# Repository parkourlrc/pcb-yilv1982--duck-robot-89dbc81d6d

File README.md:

# duck-robot

MicroDuck 小型双足机器人的个人复刻项目。当前主线为**方案 C（社区套件，飞特 HD-1910-C001）**；组织原则是“硬件复刻与整机集成 → 核心硬件自主设计；运行软件参考适配；训练环境自主建设”。A/B 仅作来源与回退标签，不作为整个项目的一级分类。

**当前状态（2026-11-05）**
- **整机**：M1 已完成（用户确认 2026-11-05）：新单 3P 口 IMU 已换装、15 颗舵机标定完成；IMU 间歇缺答/行走摔倒转可靠性跟踪。
- **自主 HAT**：B.0 / `84362651` 已付款5片；[工厂MK701/Y701方向确认](docs/references/扩展板乙版降本/engineering-feedback/research.md)已核对，待用户回复；**研发继续暂停**，未确认发货，首板未验收，原750元目标未达成。
- **PCB 全流程**：M3 进行中，B.0 / `84362651`、Y10／SMT2611051346 已付款，等待回寄与上机测试。
- **训练**：M2 已完成（官方模型上机+基本动作，用户确认）；M4 自训进行中，自训策略尚未上机。
- **里程碑**：M1/M2 已闭环；M3 PCB 全流程进行中（已下单，待回寄/上机）；M4 自训进行中；见 [MILESTONES](MILESTONES.md)。

详见 [PROGRESS](PROGRESS.md)；物料与缺口见 [BOM](BOM.md)。

## 入口

| 文档 | 用途 |
|---|---|
| [AGENTS.md](AGENTS.md) | 项目规则、目录边界与协作要求；开始前先读 |
| [PROGRESS.md](PROGRESS.md) | 当前状态、阻塞、待办与按时间倒序的记录 |
| [BOM.md](BOM.md) | C 线物料、数量与采购状态 |
| [MILESTONES.md](MILESTONES.md) | 8 个里程碑、验收标准与当前状态 |
| [docs/pcb-production-runbook.md](docs/pcb-production-runbook.md) | PCB 从需求到回寄上机的逐步运行手册 |
| [docs/README.md](docs/README.md) | 方案、测试单、图纸、照片与研究索引 |
| [hardware/README.md](hardware/README.md) | 复刻整机、取电板与自主 HAT |
| [software/README.md](software/README.md) | 本机软件适配、robotd/Studio 与部署索引 |
| [tools/README.md](tools/README.md) | 嘉立创下单、烧录依赖与开发辅助 |
| [scripts/README.md](scripts/README.md) | 跨域维护与诊断脚本 |
| [duck-robot-training](https://gitee.com/yilv1982/duck-robot-training) | 自建 real2sim2real 训练工程与资料（2026-11-10 拆分） |
| [flash/README.md](flash/README.md) | IMU 固件与烧录 |
| [references/README.md](references/README.md) | 三个上游参考库（只读） |

## 三条主线

### 1. 硬件复刻与整机集成

整机基线、装配与接线以 [hardware/replica](hardware/replica/README.md)、[BOM](BOM.md) 和 [PROGRESS](PROGRESS.md) 为准。当前 C 线为 kissqy HAT（REVA）＋新单 3P 口 IMU＋15 颗 HD-1910-C001；白色 HAT V1.2 与旧 GD32/v0.3 板仅作历史。供电按 [v2 架构](docs/power-architecture-v2.md) 的讨论基线，实物复核见[供电与扩展板实物复核](docs/references/供电与扩展板实物复核/research.md)；旧的 [HAT V1.2 测试单](docs/hat-v1.2-test.md) 不自动套用到当前板。

### 2. 核心硬件自主设计

自主 HAT 工作区在 [hardware/custom_hat](hardware/custom_hat/README.md)：现行 B.0 源 `84362651`，2026-11-05 已付款 5 片、线路暂停，首板未验收；A.1 与旧检查点在 `rev_a`、`归档` 前缀中保留。方法与复盘见[研发流程](docs/hardware-module-development-workflow.md)、[阶段复盘](docs/references/自主扩展板阶段复盘/research.md)。报价、制造放行与实物验收分开记录。

### 3. 软件适配与训练

servo-web 工作副本在 [software/servo-web](software/servo-web/SOURCE.md)；robotd 补丁见 [software/robotd-recovery](software/robotd-recovery/README.md) 与 [software/robotd-v03](software/robotd-v03/README.md)（通信补丁已撤回，Studio 适配保留）。训练工程见 [training](training/README.md)，阶段计划见 [real2sim2real 工具链](docs/real2sim2real-toolchain-plan.md)。

## 并行参考库（只读）

三套开源资料统一存放在 [references/](references/README.md)，本项目调研结论放在 [docs/references/](docs/references/README.md)。三套库只读，不修改、不合并代码、硬件配置或采购清单；历史混入的本地修改已提取到 [local-changes/](local-changes/README.md)。

| 方案 | 本地入口 | 参考内容 |
| :--- | :--- | :--- |
| A：帆哥教程 | [microduck-build-tutorial](references/microduck-build-tutorial/README.md) | Pi Zero 2 W / OpenRB / XL330 路线（回退线，基线已存档） |
| B：fanhao375 复刻研究 | [microduck-replica](references/microduck-replica/README.md) | 机械装配、电控与调试资料；兼论 XL330 与飞特路线 |
| C：jyg9 社区套件 | [microduck-community-kit](references/microduck-community-kit/README.md) | **主参考**：imu_to_dxl / banana_pcb / dxl_hub 三块板、GD32 固件与升级工具、robotd 飞特补丁、HLS 舵机调试器 |

- 方案 B 遵循其 [LICENSE](references/microduck-replica/LICENSE) 与 [NOTICE](references/microduck-replica/NOTICE.md)：不同文件许可不同，不能整目录视为 Apache-2.0 或可商用；打印 CAD 已迁往上游独立仓 [microduck-replica-cad](https://github.com/fanhao375/microduck-replica-cad)。
- 方案 C 缺口（`software/microduck_feetech/` 完整源码上游未推送、真机整定值仅可参考等）见 [PROGRESS](PROGRESS.md)「方案方向」。

## 回退线与旁支

- **A 线回退**：[阶段基线](docs/route-a-baseline-20260928.md)、[A 线 BOM](docs/bom-route-a-20260928.md)、[A 训练](https://gitee.com/yilv1982/duck-robot-training/blob/main/docs/a-training.md)、[A 验收数据](docs/a-training-validation.json)、[B 训练](docs/b-training.md)。仅回退时使用。
- **旁支研究**：[消费电子玩具市场研究](docs/references/消费电子玩具市场研究/research.md)；资料保留，不列入硬件主线。
- **历史事件**：[2026-10-31～11-02 事件摘录](docs/archive/readme-events-2026-11.md)；完整记录见 PROGRESS 与各专题。

## 致谢

感谢 [AI-FanGe/Microduck-build-tutorial](https://github.com/AI-FanGe/Microduck-build-tutorial)、[Rhoban/microban](https://github.com/Rhoban/microban)、[pollen-robotics/microduck](https://github.com/pollen-robotics/microduck) 及方案 B/C 上游作者的开源工作；各参考库内容以其自带许可为准。

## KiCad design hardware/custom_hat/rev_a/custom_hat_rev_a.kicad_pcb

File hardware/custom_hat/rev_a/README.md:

# Custom HAT Rev A.1（制造/实物验收未完成）

当前源`86654c03b6c1c8f51f7d5a4bef469aceed2ddfc73433b3e50426940c2a23164a`。新增BMI088 0.5mm/0.2mm F.Cu电源支路；邮票孔居中、X108/160分板带局部退铜；修复第二单元Power映射。原生主板/拼板全0，两个0.175mm探针均被Power0.2规则拒绝。旧r1～r17退出制造入口；实际工艺/制造/完整机械与首板未验。U301四窗69.63%、TI窗口、J301 B面等既有修复保持，见[本轮报告](../../../docs/references/扩展板邮票孔与电源修复/research.md)。 当前交付已补为20261103-assembly工序版：6THT/单元在双面SMT及支撑切断分板后逐点手工焊接，排除整板波峰/通孔再流；PCB与Gerber几何保持，实际工具/工艺待验。

## 当前文件事实

当前[双联r18](../panels/a1-smt-2up-20261102-r18/README.md)对应86654c03，85×82mm、104SMT/12THT/12POFV、402Paste及370孔；居中孔与局部退铜、两单元Power规则已核。完整PCBA包有12THT/116全坐标、118含DNP映射和装配图；旧r1～r17撤出，不能由旧DRC0判等价。

2026-11-02[国内规则自查](../../../docs/references/归档扩展板嘉立创规则自查/research.md)及[SMT专项](../../../docs/references/归档扩展板贴片规范复查/research.md)继续作为来源，RS-274-X派生包以[交付入口](../release-review/README.md)为准。U701突出铜盘和上机尺寸已有文件级方案；余项按证据逐项处理，不再等人工泛答十问。

| 项目 | 本机文件/工具核对 |
|---|---|
| 主入口 | custom_hat_rev_a.kicad_pro / .kicad_sch / .kicad_pcb；六个功能子页 |
| PCB | 65×30mm板框、4层、72封装、1132线段、100贯通via，盲/埋/微孔0 |
| 铜区 | F/B POWER_GND、In1 POWER_GND、In2 +3V3；直流焊盘连通已核，不等于完整高频回流核准 |
| 完整工程重铺铜 DRC | 已证明DRU有效加载；普通违规0、未连接0、schematic parity 0、ERC 0、netlist mismatch 0，功能与制造未验收 |
| ERC | 0，不能替代真实电路、焊盘、PCB 和功能检查 |
| 生产审查包 | production-20261102-panel-edge-review为同源X2内部审计；国内86654c03单板RS-274-X及r18完整PCBA包同步，含明确制造规格/材料与工序说明 |
| BOM | 58/58拟装器件、38/38有效分组、35唯一MPN；52贴装+6通孔；C307 DNP。分组增加仅因C309图形变体，不代表新增器件或采购核准 |
| 电源器件 | L301=5.6µH IHLP4040DZER5R6M5A；R309=WSL120600000ZEA9铜跳线，专用焊盘已匹配 |
| 安装条件 | J301 B面朝外；相向PCB表面名义间距11.6～13.33mm不含公差/线束/附件，未选隔离柱；H1/H2排母附近仍限≤4.5mm圆形头部，不加垫圈或超径六角件 |
| 环宽/热孔 | 99via环宽≥0.125mm；U701 F/内层0.35/0.15→环宽0.1，B面0.25/0.15→0.05，处公开极限，非推荐裕量；6处filled/capped要求保持，CSV逐层明确 |
| 反馈/补偿 | FB全网6.332mm、COMP4.509mm、RC1.638mm，均F.Cu；布局检查通过，环路稳定性未验收 |
| 补偿公式 | 图27理想网络与ngspice核对一致，Eq12印刷系数未当选值依据；14kΩ/3.3nF保持，未借手册示例相位裕量宣称本板通过 |
| LDO回路 | C308/C309为2.2µF；C309输出线2.227mm，R703仅串电容回地；C311并联影响已单列，未证实旧板振荡 |
| I2S参考铜 | 原线路保持；现行5条I2S取样与c6c09b33版一致。F地3片各有地via，直流同组不证明回流阻抗或EMI合格 |
| codec复位 | J101.33/ GPIO3_C3接U701.31；R308=10kΩ、C310=100nF保持，四端同组；复位GPIO驱动和实际低脉冲/电源时序待验 |
| J502扩展口 | A.1按Qwiic/STEMMA QT针号：GND/3V3/SDA/SCL；需继续核外设电平、上拉、地址、线束与负载，非所有SH4P通用 |
| 主控软件 | 历史内核同版本官方包缺codec/BMI088驱动；[codec模块/overlay](../software/codec/README.md)、[音频路由工具](../software/codec/AUDIO-ROUTING.md)及[BMI088双端点适配器](../software/imu/README.md)已离线核查；实际主控配置、播放/录音和六轴采样仍未验收 |
| 主电流铜 | 共用输入、SERVO_VBAT及主控5V内层主干/排母入口1.2mm；官方结构基线外35/内30µm，内层所选铜段模型较统一35µm增加16.67%，不标整板额定 |
| 供电边界 | 本自设计HAT仅单源供电，不支持带电USB源并供；官方V1.11图的GPIO5V与USB VBUS同网，不当作用户实物版本识别 |
| 输入标识 | J301 B面1:2S+、2:GND；40P孔在上时B面从左1→8，F面相反。见[接口说明](../../../docs/references/扩展板电路仿真工具/power-acceptance-20261031/power-interface.md)，不用于旧白色HAT |
| 功放去耦 | C323/C328位于F面，经成对VDD/GND通孔接B面U803；VDD到C328平面铜线2.947mm，另含1个通孔，非实测性能 |
| TTL去耦 | C329/C330各100nF，B面VCC线3.135/1.441mm，各经约0.8mm线接地孔；孔接F/In1/B地，完整高频回流与实际性能未验 |
| 板名/版本 | 当前DUCK HAT A.1，沿用1.0mm字高/0.15mm笔画及丝印间距规则；A.1区分J502针序，不是制造/实测标记 |
| 制造预核 | 163圆孔逐项核钻孔，652项孔铜距通过；via/PTH器件孔/NPTH规则为0.20/0.30/0.25mm，未替代加工公差与厂商接受 |
| 图纸显示/装配 | 原理图标签已整理；18个方向器件新标记完成，底面装配图镜像、CPL不再镜像；r11位号复制按实际绘制角，原生规则通过 |

## 已关闭旧问题

AP64350 独立 1–9 焊盘、BMI088 标准封装及 CSB2 DNC、TTL 两缓冲器与动力分支、I2S 方向、麦克风/功放路径、1.8V LDO、TP802 位置、内层铜区均已有文件级修复。40P pin1 设计侧已有参考依据，不再要求用户重复手量；这些不等于整板或驱动实测通过。

## 已处理事项与剩余条件

- U501周边错误铜/keepout及J301/J506通孔、焊盘/courtyard冲突已修；实物装配高度未验证。
- I2S_SDO及`R308.2 ↔ U701.7 +3V3`连通保持；U701.7焊接面via铜盘已收进原land，另三层保留较大环宽，不要求激光盲孔。详见[分层铜盘修复](../../../docs/references/归档扩展板音频芯片焊盘/research.md)，填孔盖铜与成品检查仍必要。
- 原理图/板一致性107项已逐项修正为0：库关联、显式NC、PWR_FLAG、board-only标记、DNP及字段均同步，未关闭规则；同版生产审查包已重出。
- 双面各3个fiducial已经重排，1mm圆铜、2mm阻焊开口、无锡膏、有courtyard；普通DRC为0，夹持/拼板仍需厂商确认。
- 已加入 3 个板边 `POWER_GND` 地缝合过孔；候选和主板 DRC 均保持普通违规 `0`，位置与依据见 [地缝合/EMC 复核](../../../docs/references/扩展板电路仿真工具/ground-stitch-20261030/research.md)。
- I2C5本板上拉、电容盘中孔已修。U301已有5个同网热孔，C303新增VIN线2.7025mm，C308位于LDO附近。codec/TO-252不套固定孔数。有效电容/稳定性、载流、真实热/回流、小孔加工与首板功能仍未完成，不能按孔数或评分放行。
- 既有 best、base-clean、fanout-check、via-work 与 ../candidates/ 均不是发布版。

## 工作流程

当前可交给用户审阅的[CAM/装配评审资料](../release-review/README.md)包含固定制造文件和更新后的制造状态说明，未发送。包内列明待工厂接受的孔/land/POFV/层叠和装配问题；它不是自动下单包或实物放行。

使用 ../scripts/pipeline.py 建立完整副本并检查；见[流程说明](../scripts/README.md)。不在主板上直接重跑旧布局、补孔或布线实验。每个电路/布局修复须有来源、同规则报告与检查点；通过后才能考虑回写主入口。

已确认功能为供电、TTL、板载 IMU、ToF、播放/录音；屏幕、摄像头、RS485、EEPROM、充电、UPS 不在范围。当前 GPIO 控制 DXL_DIR，不能写成自动换向已验证。默认不提交、不下单、不操作实物。

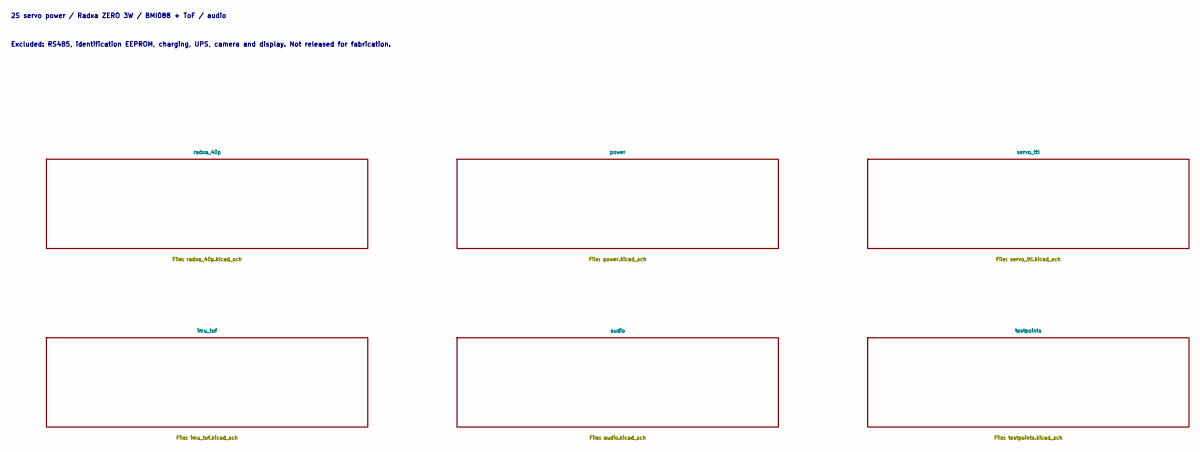
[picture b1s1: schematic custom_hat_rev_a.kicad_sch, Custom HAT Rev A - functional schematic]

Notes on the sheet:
2S servo power / Radxa ZERO 3W / BMI088 + ToF / audio
Excluded: RS485, identification EEPROM, charging, UPS, camera and display. Not released for fabrication.

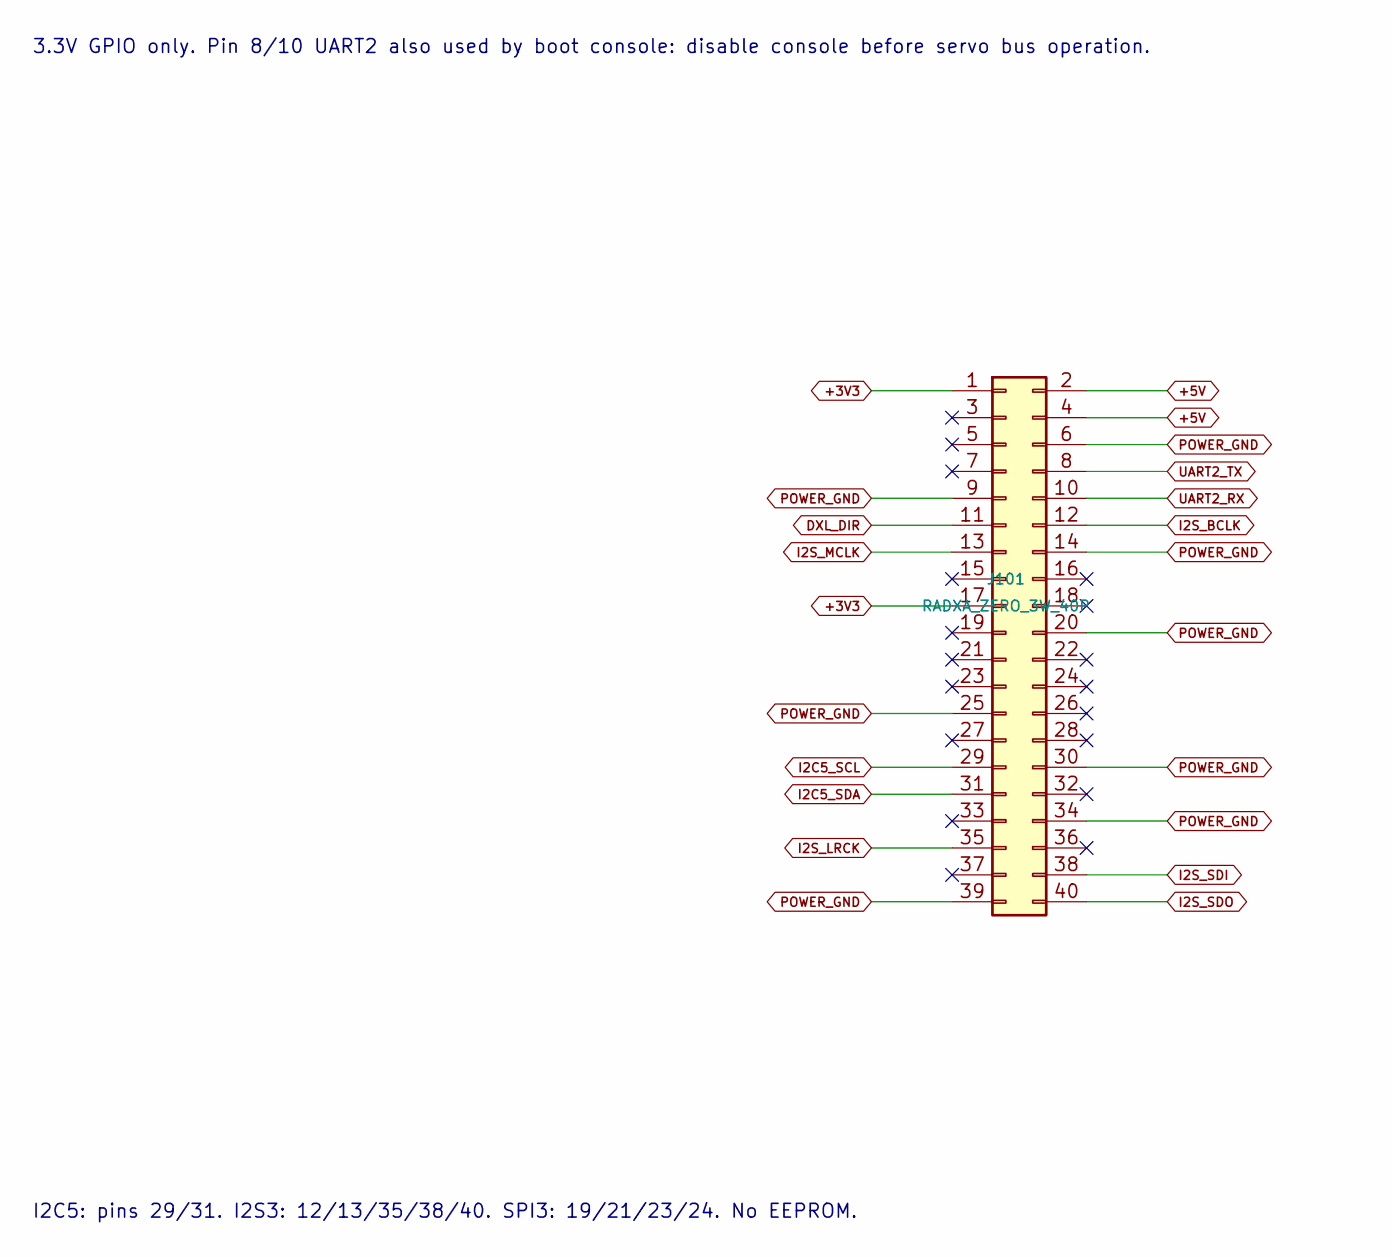
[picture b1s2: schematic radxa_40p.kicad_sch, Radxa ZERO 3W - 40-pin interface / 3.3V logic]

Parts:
J101: RADXA_ZERO_3W_40P; PinSocket_2x20_P2.54mm_Vertical

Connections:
+3V3: J101.1, J101.17; also elsewhere on the board
+5V: J101.2, J101.4; also elsewhere on the board
CODEC_RST: J101.33; also elsewhere on the board
DXL_DIR: J101.11; also elsewhere on the board
I2C5_SCL: J101.29; also elsewhere on the board
I2C5_SDA: J101.31; also elsewhere on the board
I2S_BCLK: J101.12; also elsewhere on the board
I2S_LRCK: J101.35; also elsewhere on the board
I2S_MCLK: J101.13; also elsewhere on the board
I2S_SDI: J101.38; also elsewhere on the board
I2S_SDO: J101.40; also elsewhere on the board
POWER_GND: J101.6, J101.9, J101.14, J101.20, J101.25, J101.30, J101.34, J101.39; also elsewhere on the board
UART2_RX: J101.10; also elsewhere on the board
UART2_TX: J101.8; also elsewhere on the board

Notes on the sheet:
3.3V GPIO only. Pin 8/10 UART2 also used by boot console: disable console before servo bus operation.
I2C5: pins 29/31. I2S3: 12/13/35/38/40. SPI3: 19/21/23/24. No EEPROM.

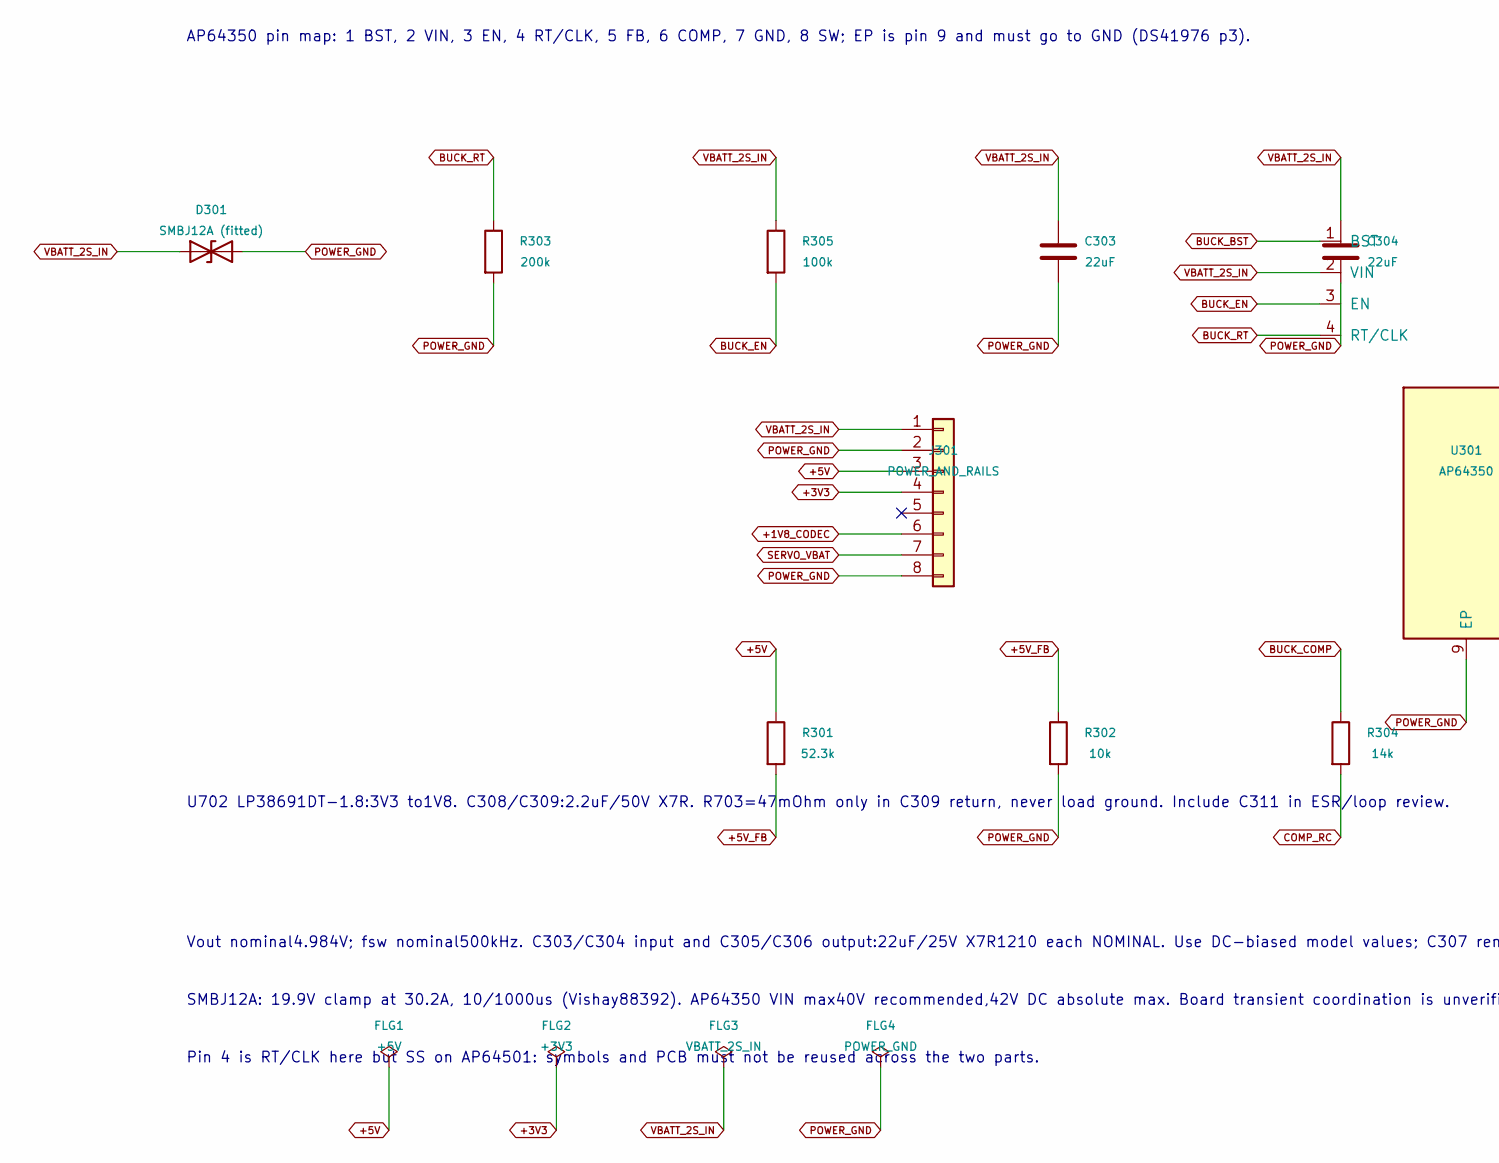
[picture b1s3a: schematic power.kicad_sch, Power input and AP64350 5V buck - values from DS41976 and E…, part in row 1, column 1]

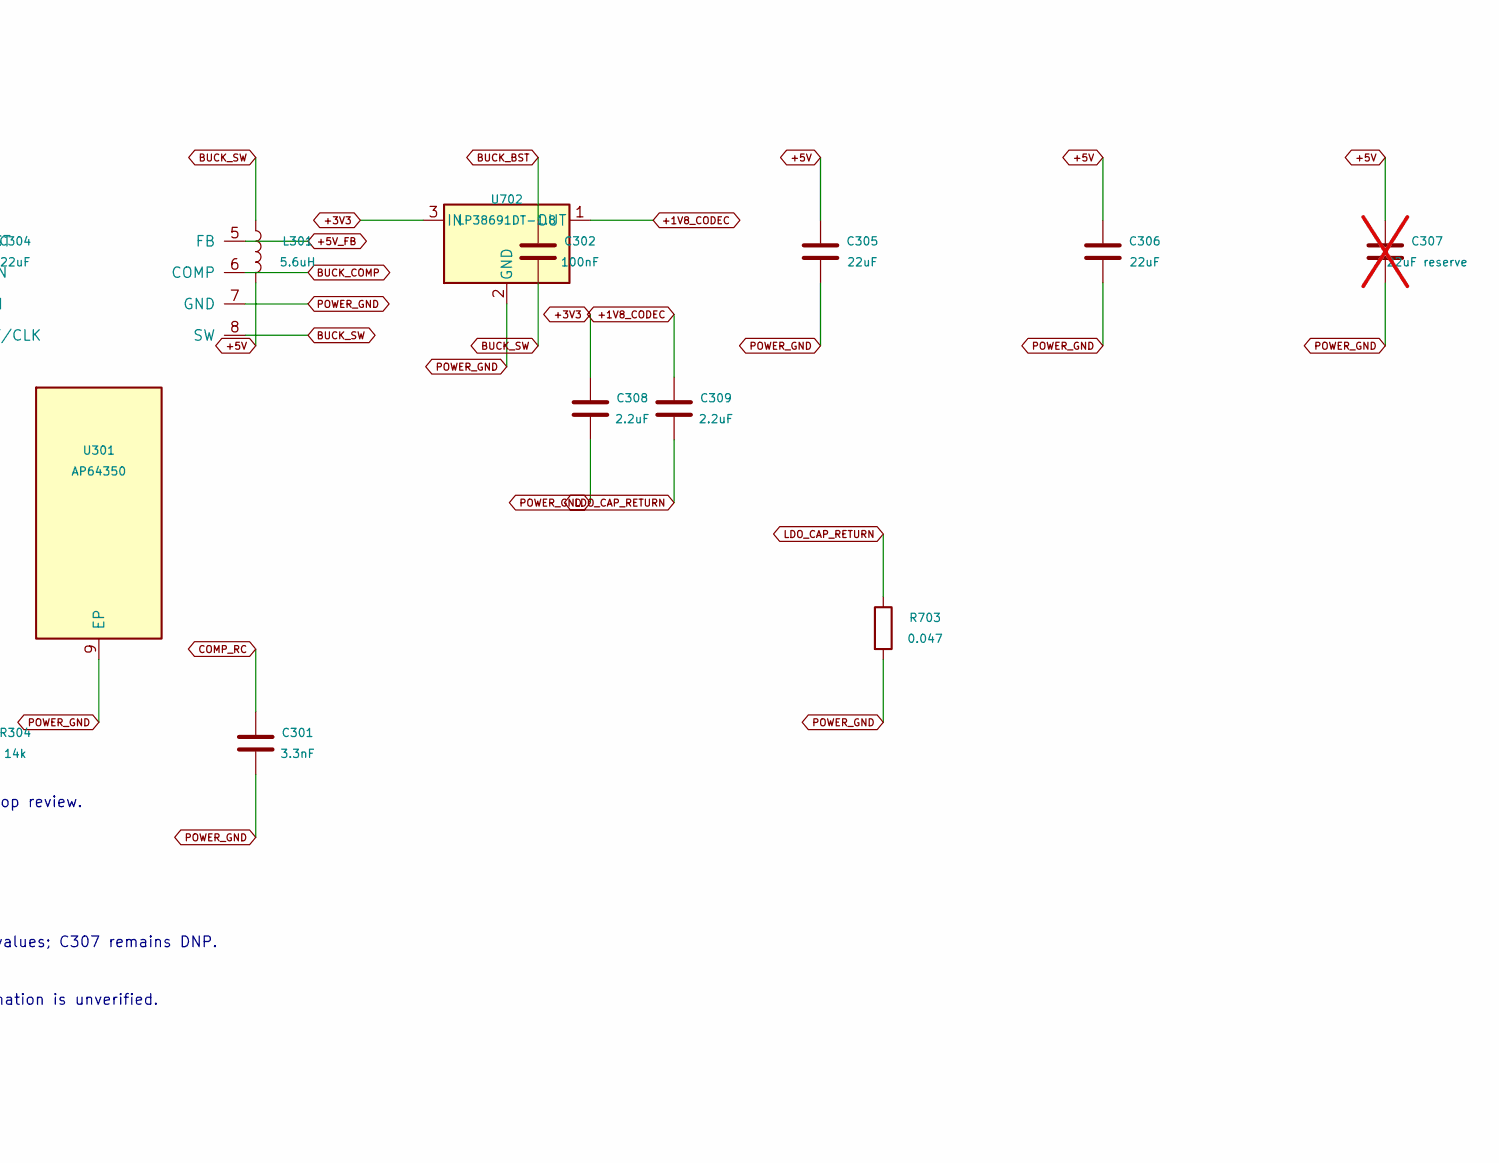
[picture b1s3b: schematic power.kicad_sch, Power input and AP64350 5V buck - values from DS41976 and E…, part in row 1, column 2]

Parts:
C301: 3.3nF; C_0805_2012Metric; Voltage Rating 50V; Tolerance 5%; MPN 08055A332JAT2A
C302: 100nF; C_0805_2012Metric; Voltage Rating 50V; Tolerance 10%; MPN C0805C104K5RACTU
C303, C304, C305, C306: 22uF; C_1210_3225Metric; Voltage Rating 25V; Tolerance 10%; MPN C1210C226K3RACTU
C307: 22uF reserve; C_1206_3216Metric; Voltage Rating 16V; Tolerance 20%; MPN C1206C226M4PACTU; not fitted
C308: 2.2uF; C_0805_2012Metric; Voltage Rating 50V; Tolerance 10%; MPN C0805C225K5RACTU
C309: 2.2uF; C_0805_2012Metric_LDO_ClearSilk; Voltage Rating 50V; Tolerance 10%; MPN C0805C225K5RACTU
D301: SMBJ12A (fitted); D_SMB; Voltage Rating 12V VRWM; MPN SMBJ12A-E3/52
FLG1: +5V
FLG2: +3V3
FLG3: VBATT_2S_IN
FLG4: POWER_GND
J301: POWER_AND_RAILS; Samtec_TSW108_07; MPN TSW-108-07-G-S
L301: 5.6uH; IHLP4040DZ_5A_Above2u2; MPN IHLP4040DZER5R6M5A
R301: 52.3k; R_0805_2012Metric; MPN CRCW080552K3FKEA
R302: 10k; R_0805_2012Metric; MPN CRCW080510K0FKEA
R303: 200k; R_0805_2012Metric; MPN CRCW0805200KFKEA
R304: 14k; R_0805_2012Metric; MPN CRCW080514K0FKEA
R305: 100k; R_0805_2012Metric; MPN CRCW0805100KFKEA
R703: 0.047; Vishay_WSLP0603_Damping; Tolerance 1%; Power Rating 0.4W at70C; derate above70C; MPN WSLP0603R0470FEA
U301: AP64350; SO8EP_AP64350_Paste4_Project; MPN AP64350SP-13
U702: LP38691DT-1.8; TI_NDP0003B_LP38691_PasteGrid; MPN LP38691DT-1.8/NOPB

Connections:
+1V8_CODEC: C309.1, J301.6, U702.1 (OUT); also elsewhere on the board
+3V3: C308.1, FLG2.1, J301.4, U702.3 (IN); also elsewhere on the board
+5V: C305.1, C306.1, C307.1, FLG1.1, J301.3, L301.2, R301.1; also elsewhere on the board
+5V_FB: R301.2, R302.1, U301.5 (FB)
BUCK_BST: C302.1, U301.1 (BST)
BUCK_COMP: R304.1, U301.6 (COMP)
BUCK_EN: R305.2, U301.3 (EN)
BUCK_RT: R303.1, U301.4 (RT/CLK)
BUCK_SW: C302.2, L301.1, U301.8 (SW)
COMP_RC: C301.1, R304.2
LDO_CAP_RETURN: C309.2, R703.1
POWER_GND: C301.2, C303.2, C304.2, C305.2, C306.2, C307.2, C308.2, D301.2 (A2), FLG4.1, J301.2, J301.8, R302.2, R303.2, R703.2, U301.7 (GND), U301.9 (EP), U702.2 (GND); also elsewhere on the board
SERVO_VBAT: J301.7; also elsewhere on the board
VBATT_2S_IN: C303.1, C304.1, D301.1 (A1), FLG3.1, J301.1, R305.1, U301.2 (VIN); also elsewhere on the board

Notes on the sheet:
AP64350 pin map: 1 BST, 2 VIN, 3 EN, 4 RT/CLK, 5 FB, 6 COMP, 7 GND, 8 SW; EP is pin 9 and must go to GND (DS41976 p3).
Vout nominal4.984V; fsw nominal500kHz. C303/C304 input and C305/C306 output:22uF/25V X7R1210 each NOMINAL. Use DC-biased model values; C307 remains DNP.
U702 LP38691DT-1.8:3V3 to1V8. C308/C309:2.2uF/50V X7R. R703=47mOhm only in C309 return, never load ground. Include C311 in ESR/loop review.
SMBJ12A: 19.9V clamp at 30.2A, 10/1000us (Vishay88392). AP64350 VIN max40V recommended,42V DC absolute max. Board transient coordination is unverified.
Pin 4 is RT/CLK here but SS on AP64501: symbols and PCB must not be reused across the two parts.

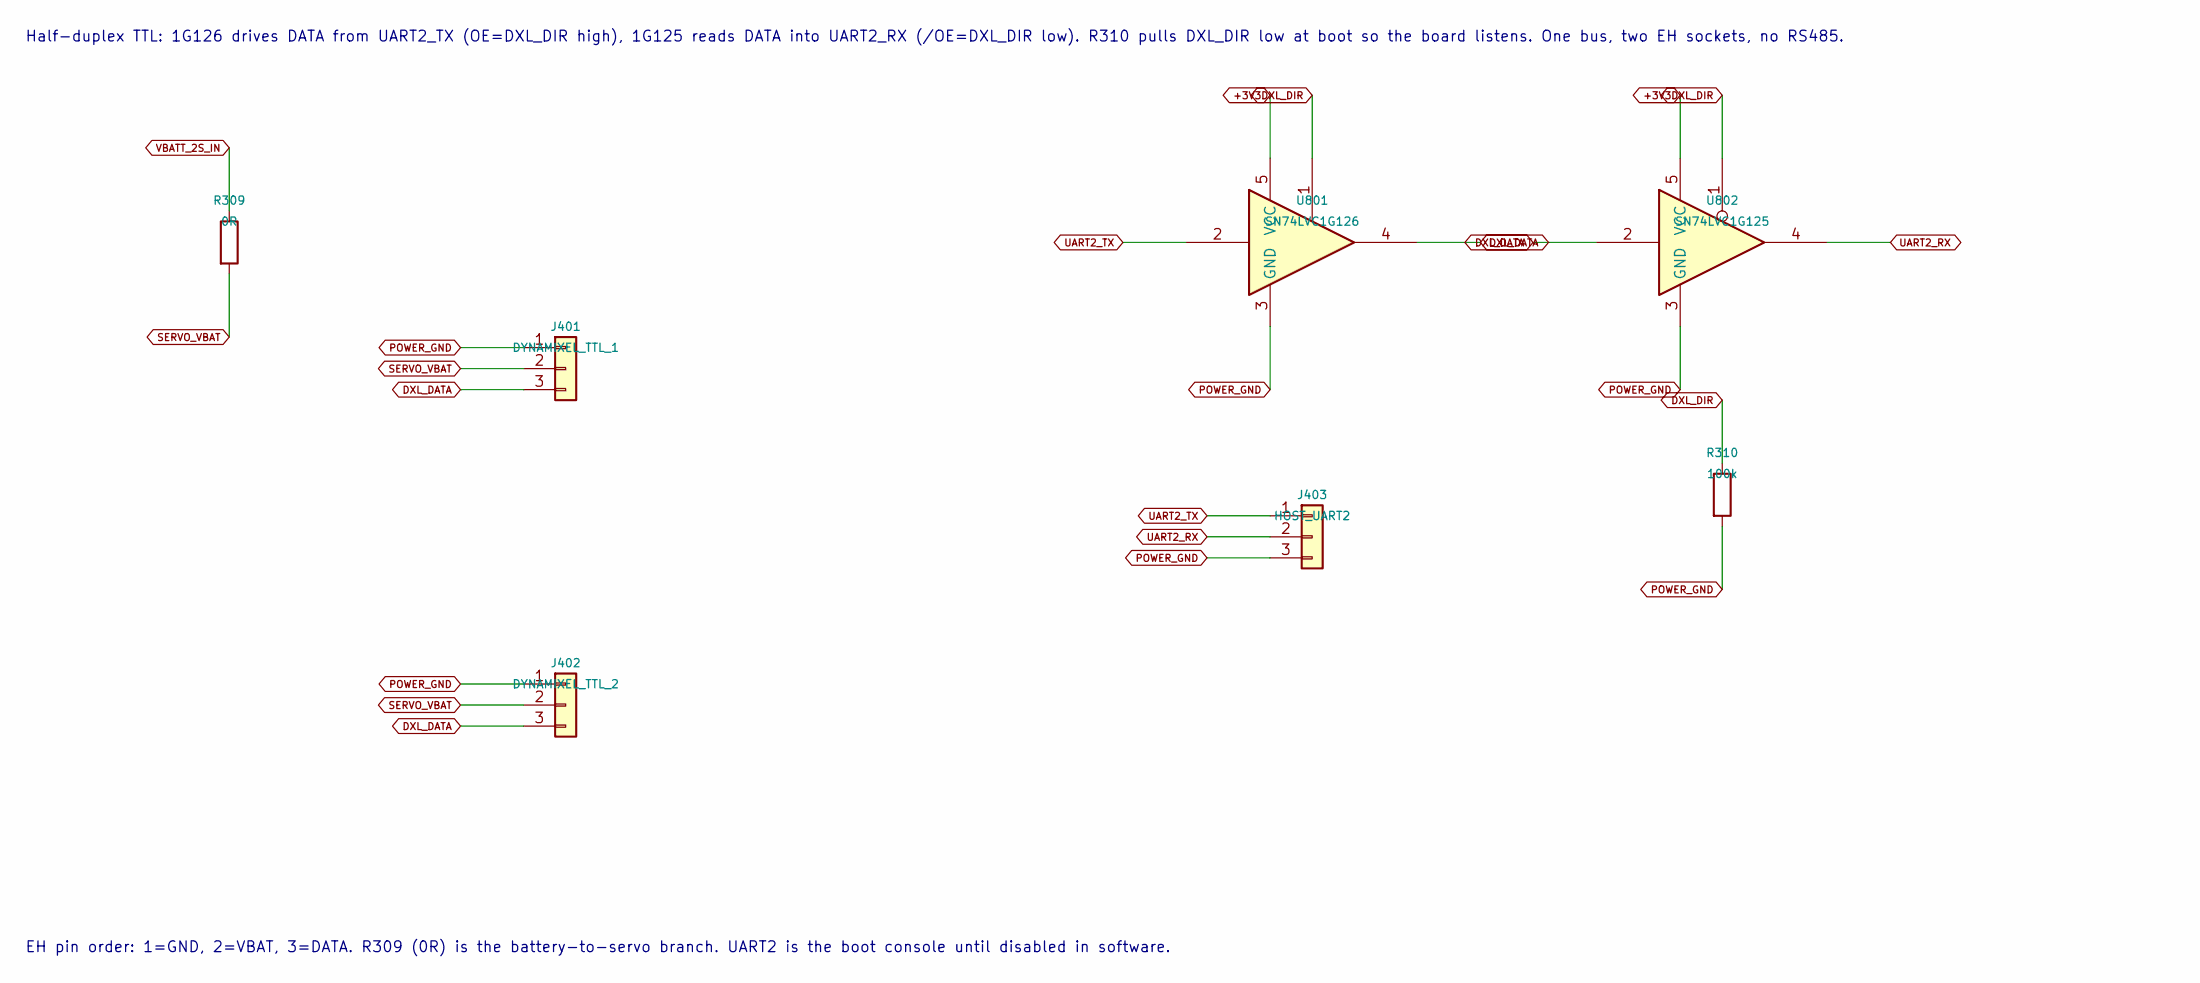
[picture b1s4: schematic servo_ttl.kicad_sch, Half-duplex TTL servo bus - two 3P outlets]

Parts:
J401: DYNAMIXEL_TTL_1; JST_EH_B3B-EH-A_1x03_P2.50mm_Vertical
J402: DYNAMIXEL_TTL_2; JST_EH_B3B-EH-A_1x03_P2.50mm_Vertical
J403: HOST_UART2; PinHeader_1x03_P2.54mm_Vertical
R309: 0R; R_1206_3216Metric
R310: 100k; R_0402_1005Metric
U801: SN74LVC1G126; SOT-23-5
U802: SN74LVC1G125; SOT-23-5

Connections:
+3V3: U801.5 (VCC), U802.5 (VCC); also elsewhere on the board
DXL_DATA: J401.3, J402.3, U801.4, U802.2
DXL_DIR: R310.1, U801.1, U802.1; also elsewhere on the board
POWER_GND: J401.1, J402.1, J403.3, R310.2, U801.3 (GND), U802.3 (GND); also elsewhere on the board
SERVO_VBAT: J401.2, J402.2, R309.2; also elsewhere on the board
UART2_RX: J403.2, U802.4; also elsewhere on the board
UART2_TX: J403.1, U801.2; also elsewhere on the board
VBATT_2S_IN: R309.1; also elsewhere on the board

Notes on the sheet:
Half-duplex TTL: 1G126 drives DATA from UART2_TX (OE=DXL_DIR high), 1G125 reads DATA into UART2_RX (/OE=DXL_DIR low). R310 pulls DXL_DIR low at boot so the board listens. One bus, two EH sockets, no RS485.
EH pin order: 1=GND, 2=VBAT, 3=DATA. R309 (0R) is the battery-to-servo branch. UART2 is the boot console until disabled in software.

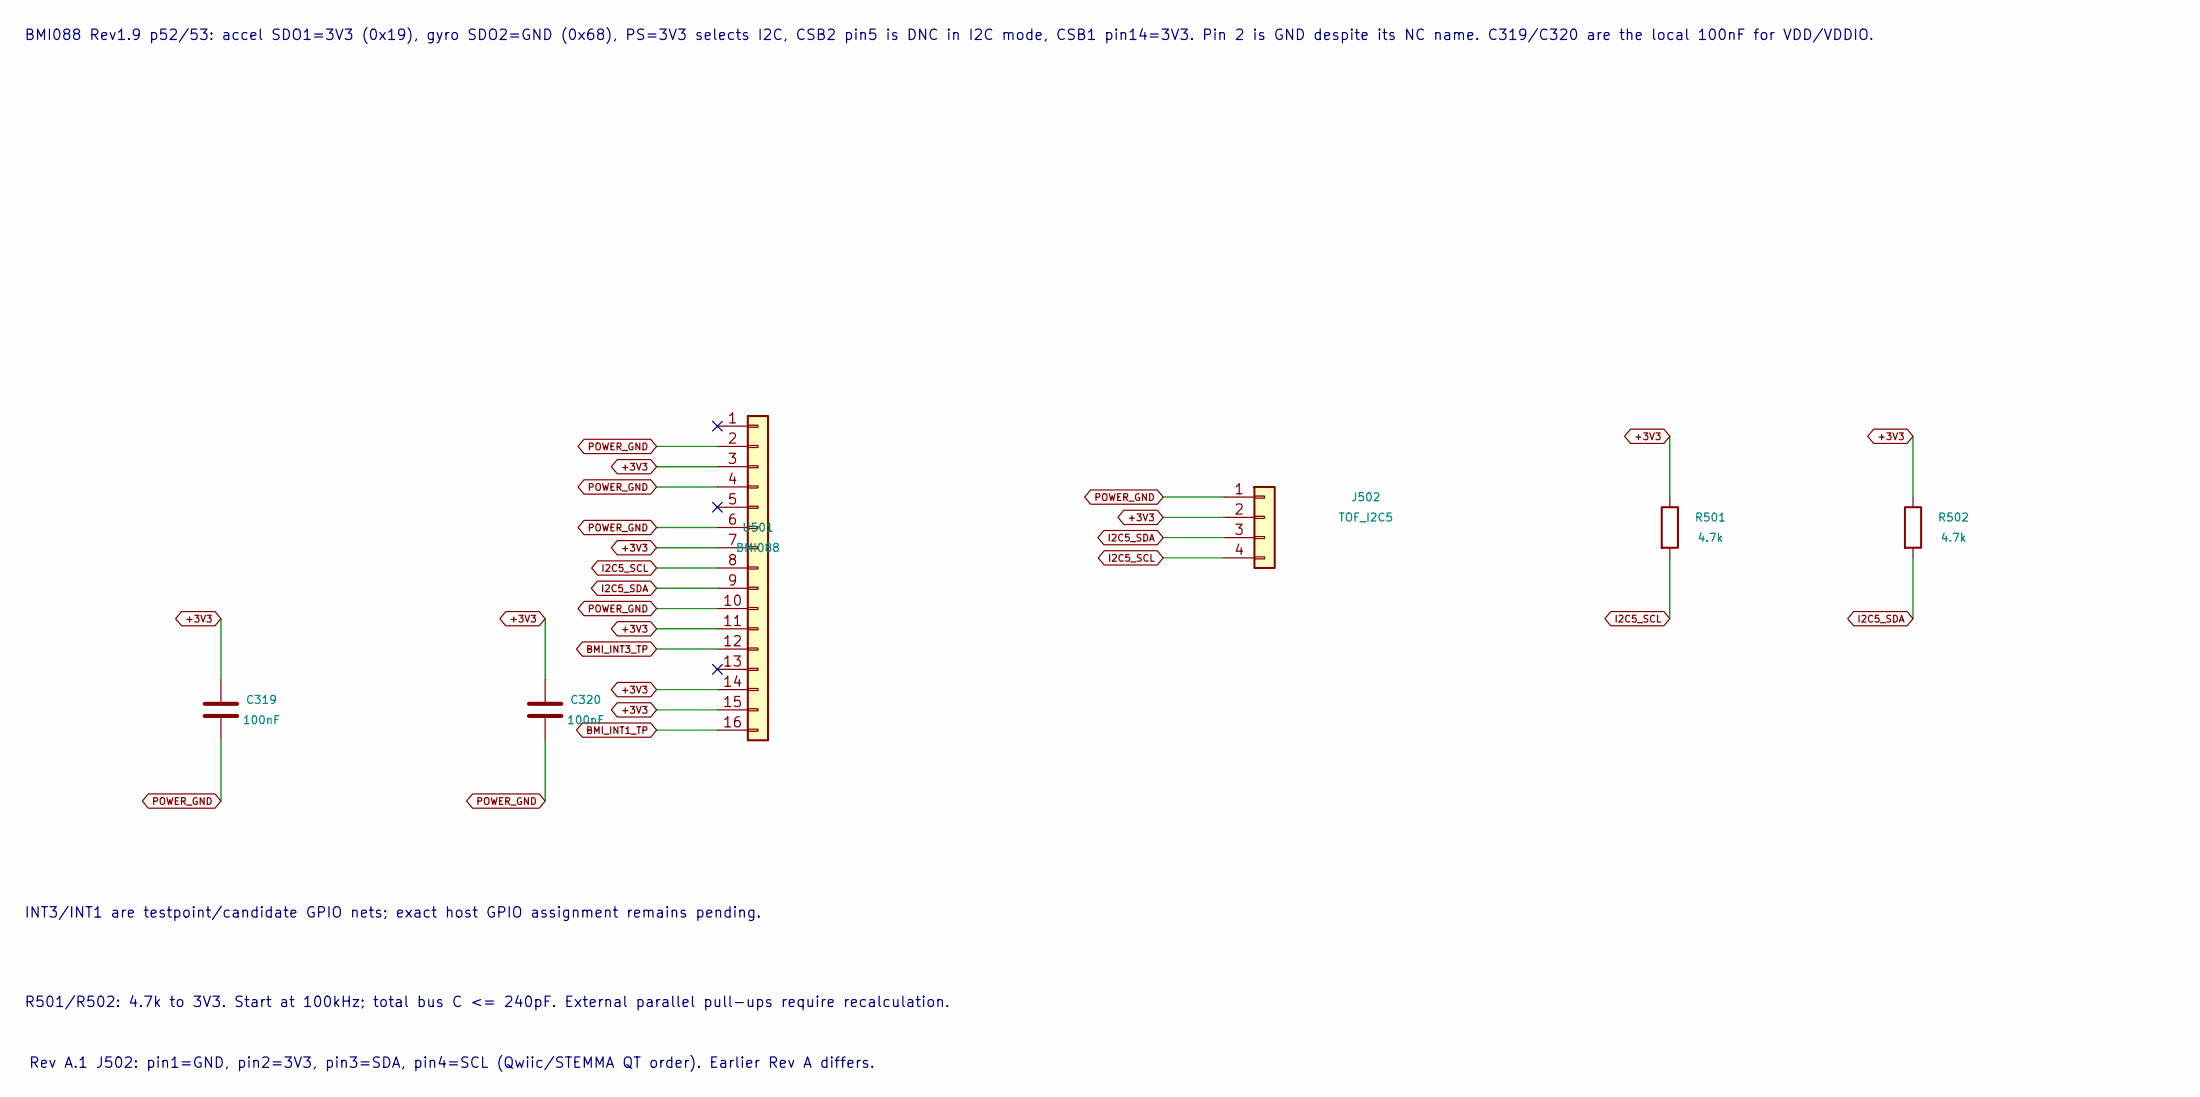
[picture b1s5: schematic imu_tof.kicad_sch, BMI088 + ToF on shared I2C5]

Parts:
C319, C320: 100nF; C_0402_1005Metric; Voltage Rating 25V; Tolerance 10%; MPN C0402C104K3RACTU
J502: TOF_I2C5; JST_SH_BM04B-SRSS-TB_1x04-1MP_P1.00mm_Vertical; MPN BM04B-SRSS-TB(LF)(SN)
R501, R502: 4.7k; R_0402_1005Metric; MPN CRCW04024K70FKED
U501: BMI088; Bosch_LGA-16_4.5x3mm_P0.5mm_LayoutBorder7x1y_ClockwisePinNu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; MPN BMI088

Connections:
+3V3: C319.1, C320.1, J502.2, R501.1, R502.1, U501.3, U501.7, U501.11, U501.14, U501.15; also elsewhere on the board
BMI_INT1_TP: U501.16; also elsewhere on the board
BMI_INT3_TP: U501.12; also elsewhere on the board
I2C5_SCL: J502.4, R501.2, U501.8; also elsewhere on the board
I2C5_SDA: J502.3, R502.2, U501.9; also elsewhere on the board
POWER_GND: C319.2, C320.2, J502.1, U501.2, U501.4, U501.6, U501.10; also elsewhere on the board

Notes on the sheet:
BMI088 Rev1.9 p52/53: accel SDO1=3V3 (0x19), gyro SDO2=GND (0x68), PS=3V3 selects I2C, CSB2 pin5 is DNC in I2C mode, CSB1 pin14=3V3. Pin 2 is GND despite its NC name. C319/C320 are the local 100nF for VDD/VDDIO.
INT3/INT1 are testpoint/candidate GPIO nets; exact host GPIO assignment remains pending.
R501/R502: 4.7k to 3V3. Start at 100kHz; total bus C <= 240pF. External parallel pull-ups require recalculation.
Rev A.1 J502: pin1=GND, pin2=3V3, pin3=SDA, pin4=SCL (Qwiic/STEMMA QT order). Earlier Rev A differs.
